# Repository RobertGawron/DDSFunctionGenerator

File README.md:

# 6MHz DDS Function Generator

**This project is unfinished.**

## Summary

A function generator is a laboratory instrument used to generate various electrical waveforms. This project utilizes DDS  [DDS (direct digital synthesis)](https://en.wikipedia.org/wiki/Direct_digital_synthesis), a technique that allows the creation of arbitrary waveforms from a single base frequency.

## Current Version

The current version of the PCB uses components with 0402 (or similar) footprints. Use of these components wasn’t the best choice - they're too difficult to solder, and there was no need to minimize the board size. The next version of the PCB will switch to 0805 components for easier assembly.

## System Architecture

Tools: PlantUML

## Hardware

Tools: KiCad (for PCB design).

## Software

Tools:
* **Business Logic:** Written in Forth, a stack-based programming language designed for embedded systems and control applications.
* **Drivers:** Developed in C++17.
* **Hardware Abstraction Layer (HAL):** Auto-generated using CubeMX, a tool from STMicroelectronics.

## Simulation

This project includes an LCD for user interaction. To simplify the creation of the layout, a simulation environment has been developed. 

This simulation combines the following:
* **UI:** Built using PyQt for rendering the LCD layout and facilitating user interaction.
* **Business Logic:** Reuses the core firmware logic directly from the hardware codebase.
* HAL and Driver Mocks: Created in C++.

[More Info](./Simulation/FirmwarePCSimulator/README.md)

## Enclosure

The device's enclosure is designed using **OpenSCAD**, a script-based 3D CAD modeler that allows precise and parametric design.

[More Info](./Mechanic/MechanicOverview/README.md)

## Devops

Repetitive setup tasks are best left to automation, which is why the development environment is managed with Docker. This approach eliminates the need to deal with outdated installation lists or READMEs—just run the container, and everything is ready to go.

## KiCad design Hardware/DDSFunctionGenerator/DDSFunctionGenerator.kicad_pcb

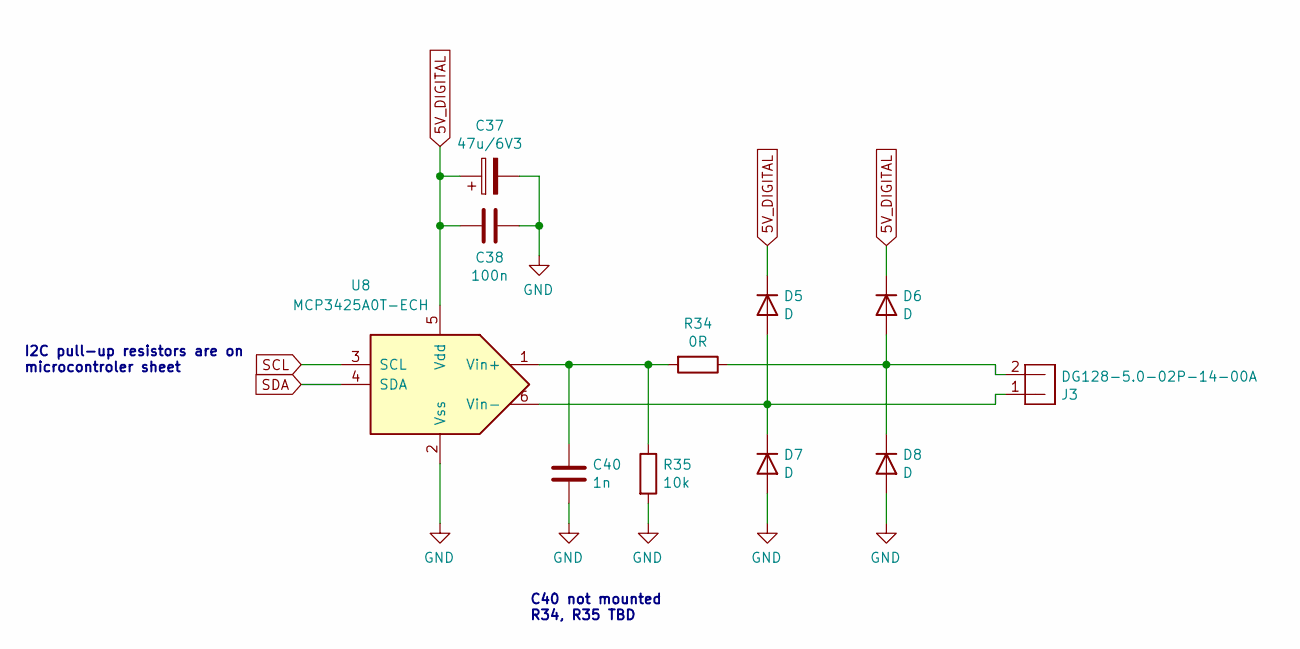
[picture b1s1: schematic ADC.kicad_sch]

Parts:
C37: 47u/6V3; CP_EIA-3528-21_Kemet-B
C38: 100n; C_0805_2012Metric
C40: 1n; C_0805_2012Metric
D5, D6, D7, D8: D; D_MiniMELF
J3: DG128-5.0-02P-14-00A
R34: 0R; R_0805_2012Metric
R35: 10k; R_0805_2012Metric
U8: MCP3425A0T-ECH; SOT-23-6_Handsoldering

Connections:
5V_DIGITAL: C37.1, C38.2, D5.1 (K), D6.1 (K), U8.5 (Vdd); also elsewhere on the board
GND: C37.2, C38.1, C40.2, D7.2 (A), D8.2 (A), R35.2, U8.2 (Vss); also elsewhere on the board
unnamed: D5.2 (A), D7.1 (K), J3.1, U8.6 (Vin-)
unnamed: D6.2 (A), D8.1 (K), J3.2, R34.1
unnamed: C40.1, R34.2, R35.1, U8.1 (Vin+)
SCL: U8.3 (SCL); also elsewhere on the board
SDA: U8.4 (SDA); also elsewhere on the board

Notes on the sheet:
I2C pull-up resistors are on microcontroler sheet
C40 not mounted R34, R35 TBD

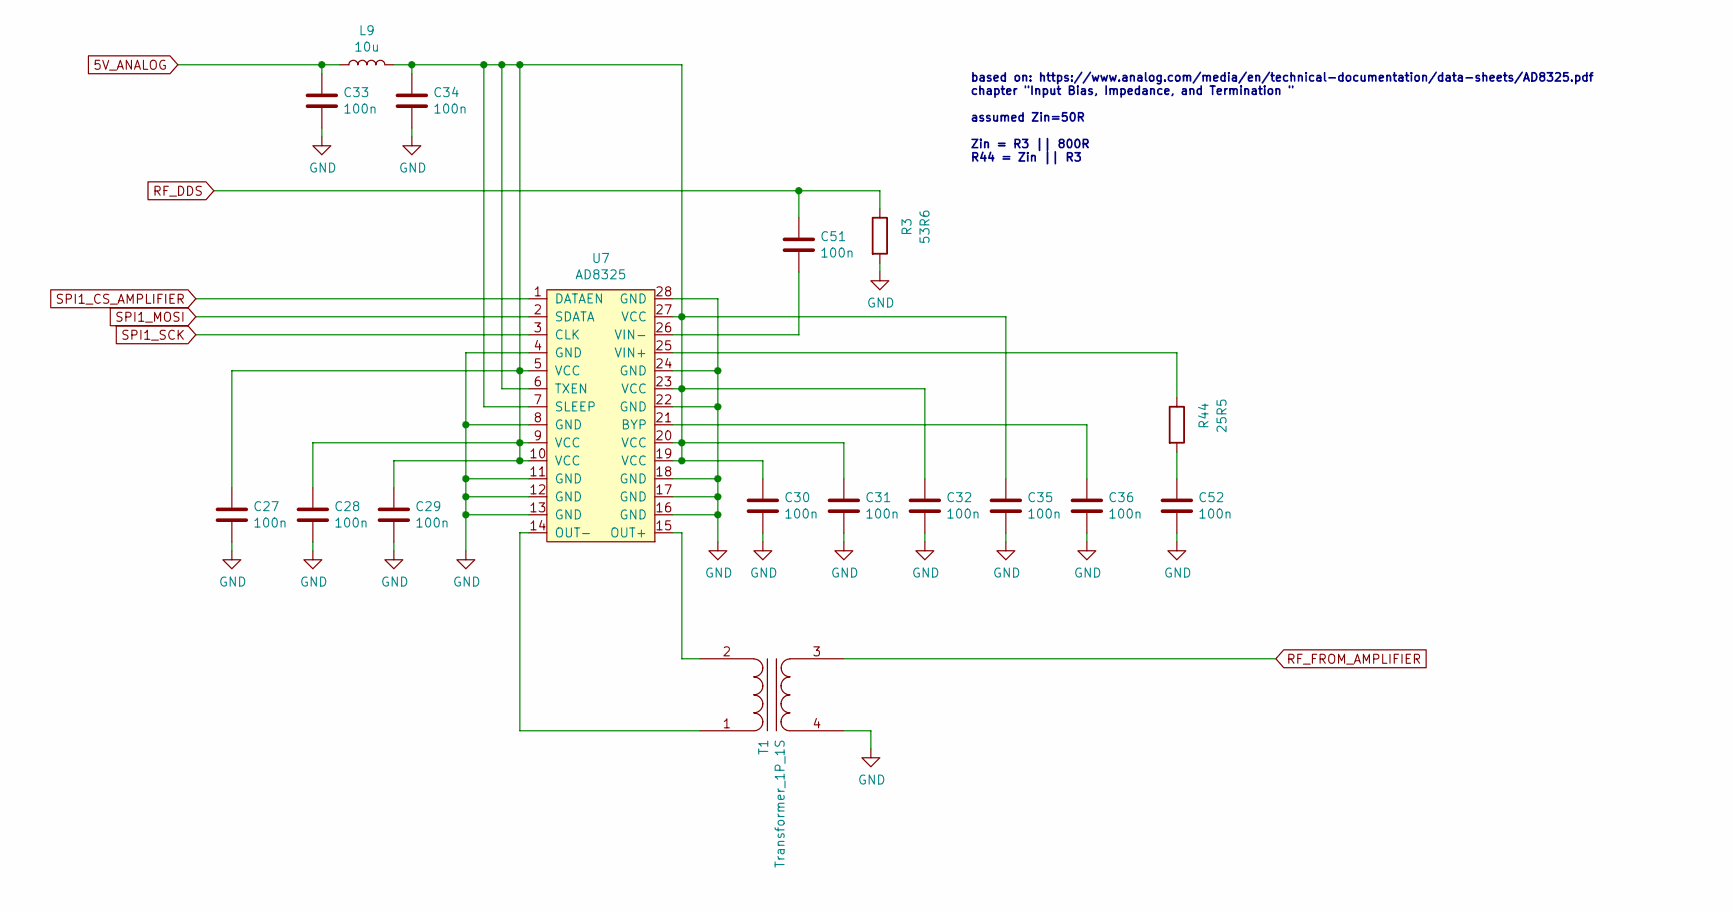
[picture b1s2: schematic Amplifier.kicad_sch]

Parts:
C27, C28, C29, C30, C31, C32, C33, C34, C35, C36, C51, C52: 100n; C_0805_2012Metric
L9: 10u; L_0805_2012Metric
R3: 53R6; R_0805_2012Metric
R44: 25R5; R_0805_2012Metric
T1: Transformer_1P_1S; Transformer_B62152_8.3
U7: AD8325; TSSOP-28_4.4x9.7mm_P0.65mm

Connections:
5V_ANALOG: C33.1, L9.1; also elsewhere on the board
GND: C27.2, C28.2, C29.1, C30.2, C31.2, C32.2, C33.2, C34.2, C35.2, C36.2, C52.2, R3.2, T1.4 (SB), U7.4 (GND), U7.8 (GND), U7.11 (GND), U7.12 (GND), U7.13 (GND), U7.16 (GND), U7.17 (GND), U7.18 (GND), U7.22 (GND), U7.24 (GND), U7.28 (GND); also elsewhere on the board
unnamed: C52.1, R44.2
unnamed: T1.1 (AA), U7.14 (OUT-)
unnamed: T1.2 (AB), U7.15 (OUT+)
unnamed: C36.1, U7.21 (BYP)
unnamed: C27.1, C28.1, C29.2, C30.1, C31.1, C32.1, C34.1, C35.1, L9.2, U7.5 (VCC), U7.6 (TXEN), U7.7 (SLEEP), U7.9 (VCC), U7.10 (VCC), U7.19 (VCC), U7.20 (VCC), U7.23 (VCC), U7.27 (VCC)
unnamed: R44.1, U7.25 (VIN+)
unnamed: C51.2, U7.26 (VIN-)
RF_DDS: C51.1, R3.1; also elsewhere on the board
RF_FROM_AMPLIFIER: T1.3 (SA); also elsewhere on the board
SPI1_CS_AMPLIFIER: U7.1 (DATAEN); also elsewhere on the board
SPI1_MOSI: U7.2 (SDATA); also elsewhere on the board
SPI1_SCK: U7.3 (CLK); also elsewhere on the board

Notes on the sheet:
based on: https://www.analog.com/media/en/technical-documentation/data-sheets/AD8325.pdf chapter "Input Bias, Impedance, and Termination " assumed Zin=50R Zin = R3 || 800R R44 = Zin || R3

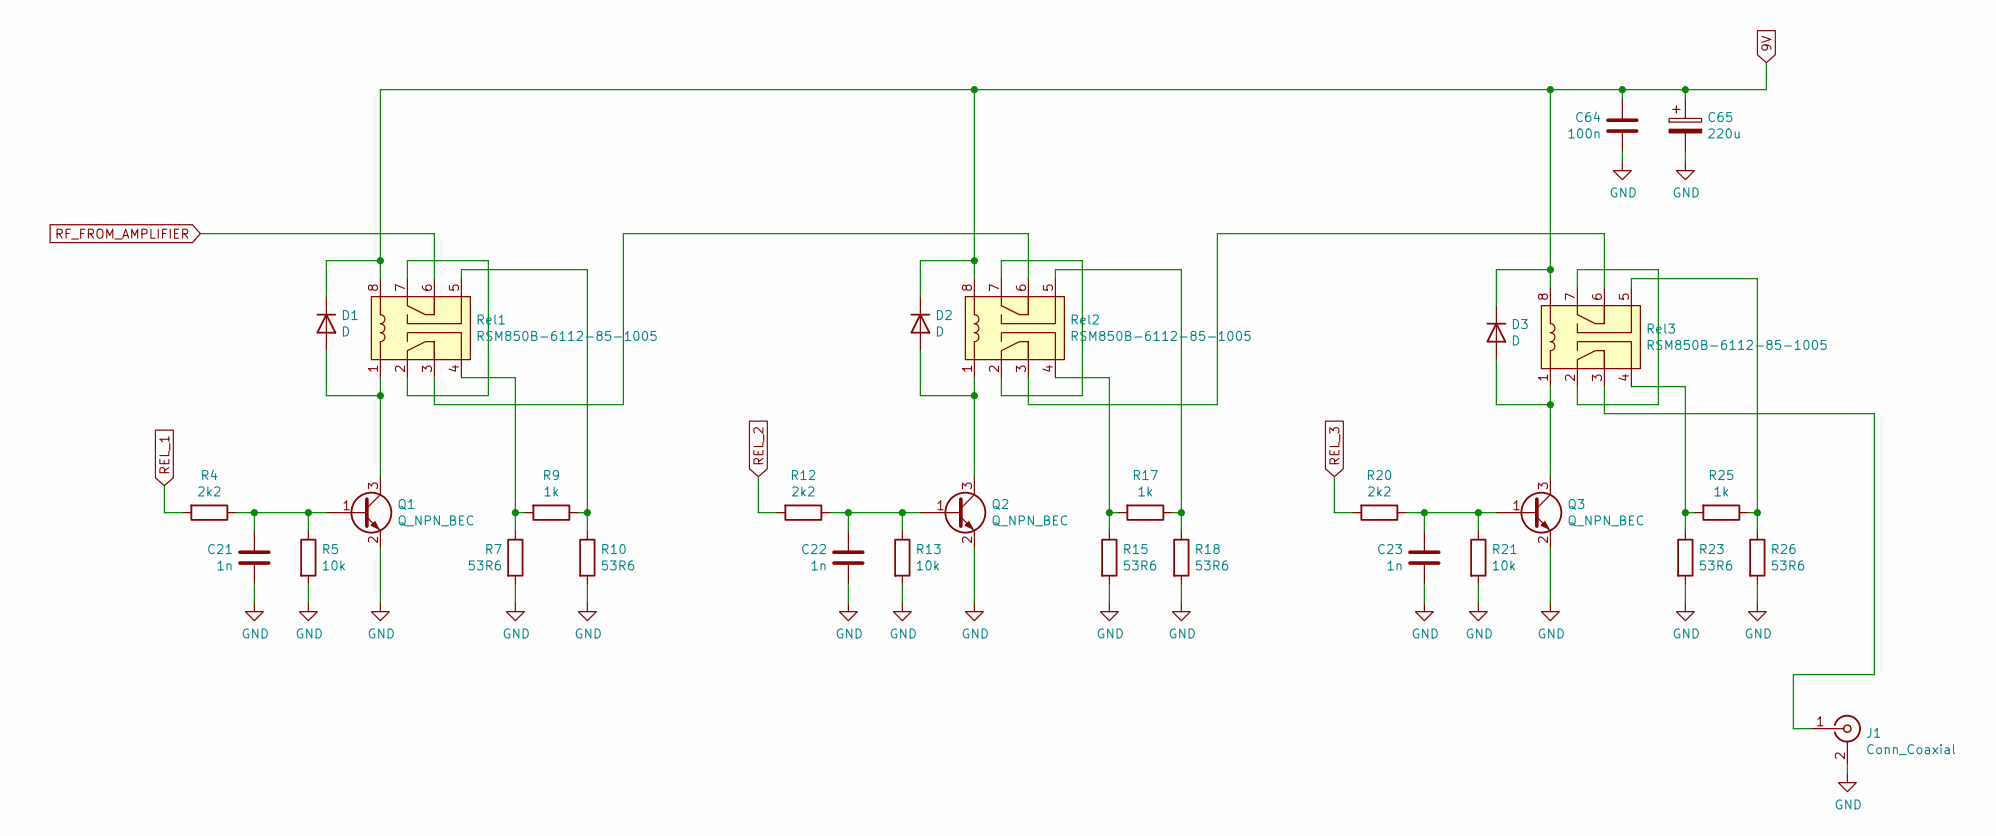
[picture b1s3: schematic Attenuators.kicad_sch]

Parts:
C21, C22, C23: 1n; C_0805_2012Metric
C64: 100n; C_0805_2012Metric
C65: 220u; CP_Elec_6.3x5.8
D1, D2, D3: D; D_MiniMELF
J1: Conn_Coaxial; BNC_Amphenol_B6252HB-NPP3G-50_Horizontal
Q1, Q2, Q3: Q_NPN_BEC; SOT-323_SC-70
R4, R12, R20: 2k2; R_0805_2012Metric
R5, R13, R21: 10k; R_0805_2012Metric
R7, R10, R15, R18, R23, R26: 53R6; R_0805_2012Metric
R9, R17, R25: 1k; R_0805_2012Metric
Rel1, Rel2, Rel3: RSM850B-6112-85-1005; Relay_DPDT_Omron_G6K-2P-Y

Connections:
9V: C64.1, C65.1, D1.1 (K), D2.1 (K), D3.1 (K), Rel1.8, Rel2.8, Rel3.8; also elsewhere on the board
GND: C21.2, C22.2, C23.2, C64.2, C65.2, J1.2 (Ext), Q1.2 (E), Q2.2 (E), Q3.2 (E), R5.2, R7.2, R10.2, R13.2, R15.2, R18.2, R21.2, R23.2, R26.2; also elsewhere on the board
unnamed: D1.2 (A), Q1.3 (C), Rel1.1
unnamed: D2.2 (A), Q2.3 (C), Rel2.1
unnamed: D3.2 (A), Q3.3 (C), Rel3.1
unnamed: J1.1 (In), Rel3.3
unnamed: C21.1, Q1.1 (B), R4.1, R5.1
unnamed: C22.1, Q2.1 (B), R12.1, R13.1
unnamed: C23.1, Q3.1 (B), R20.1, R21.1
unnamed: R7.1, R9.2, Rel1.4
unnamed: R9.1, R10.1, Rel1.5
unnamed: R15.1, R17.2, Rel2.4
unnamed: R17.1, R18.1, Rel2.5
unnamed: R23.1, R25.2, Rel3.4
unnamed: R25.1, R26.1, Rel3.5
unnamed: Rel1.2, Rel1.7
unnamed: Rel1.3, Rel2.6
unnamed: Rel2.2, Rel2.7
unnamed: Rel2.3, Rel3.6
unnamed: Rel3.2, Rel3.7
REL_1: R4.2; also elsewhere on the board
REL_2: R12.2; also elsewhere on the board
REL_3: R20.2; also elsewhere on the board
RF_FROM_AMPLIFIER: Rel1.6; also elsewhere on the board

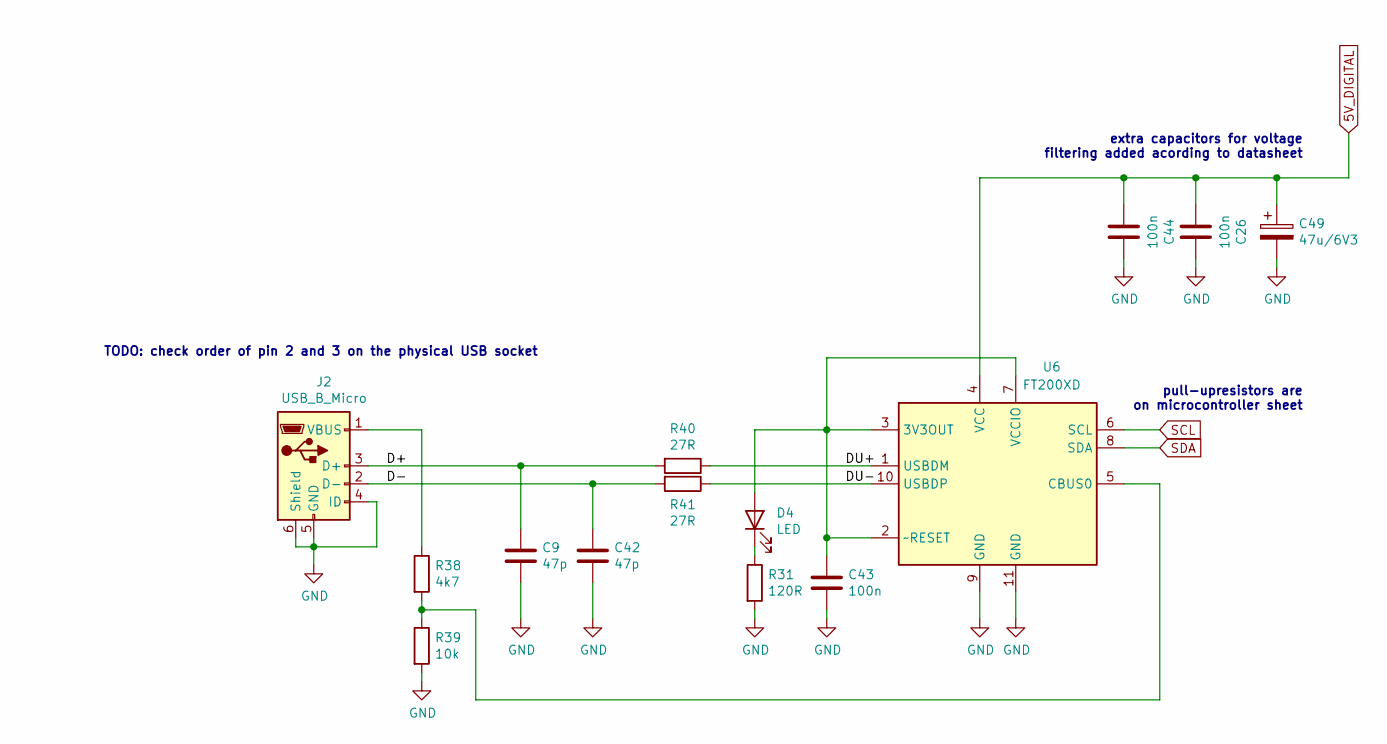
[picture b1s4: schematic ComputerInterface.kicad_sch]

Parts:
C9, C42: 47p; C_0805_2012Metric
C26, C43, C44: 100n; C_0805_2012Metric
C49: 47u/6V3; CP_EIA-3528-21_Kemet-B
D4: LED; LED_0402_1005Metric
J2: USB_B_Micro; USB_Micro-B_Molex_47346-0001
R31: 120R; R_0805_2012Metric
R38: 4k7; R_0805_2012Metric
R39: 10k; R_0805_2012Metric
R40, R41: 27R; R_0805_2012Metric
U6: FT200XD; DFN-10-1EP_3x3mm_P0.5mm_EP1.55x2.48mm

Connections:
5V_DIGITAL: C26.1, C44.1, C49.1, U6.4 (VCC); also elsewhere on the board
/ComputerInterface/D+: C9.2, J2.3 (D+), R40.2
/ComputerInterface/D-: C42.2, J2.2 (D-), R41.2
/ComputerInterface/DU+: R40.1, U6.1 (USBDM)
/ComputerInterface/DU-: R41.1, U6.10 (USBDP)
GND: C9.1, C26.2, C42.1, C43.1, C44.2, C49.2, J2.4 (ID), J2.5 (GND), J2.6 (Shield), R31.2, R39.2, U6.9 (GND), U6.11 (GND); also elsewhere on the board
unnamed: C43.2, D4.2 (A), U6.2 (~RESET), U6.3 (3V3OUT), U6.7 (VCCIO)
unnamed: D4.1 (K), R31.1
unnamed: J2.1 (VBUS), R38.1
unnamed: R38.2, R39.1, U6.5 (CBUS0)
SCL: U6.6 (SCL); also elsewhere on the board
SDA: U6.8 (SDA); also elsewhere on the board

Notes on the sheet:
extra capacitors for voltage filtering added acording to datasheet
TODO: check order of pin 2 and 3 on the physical USB socket
pull-upresistors are on microcontroller sheet

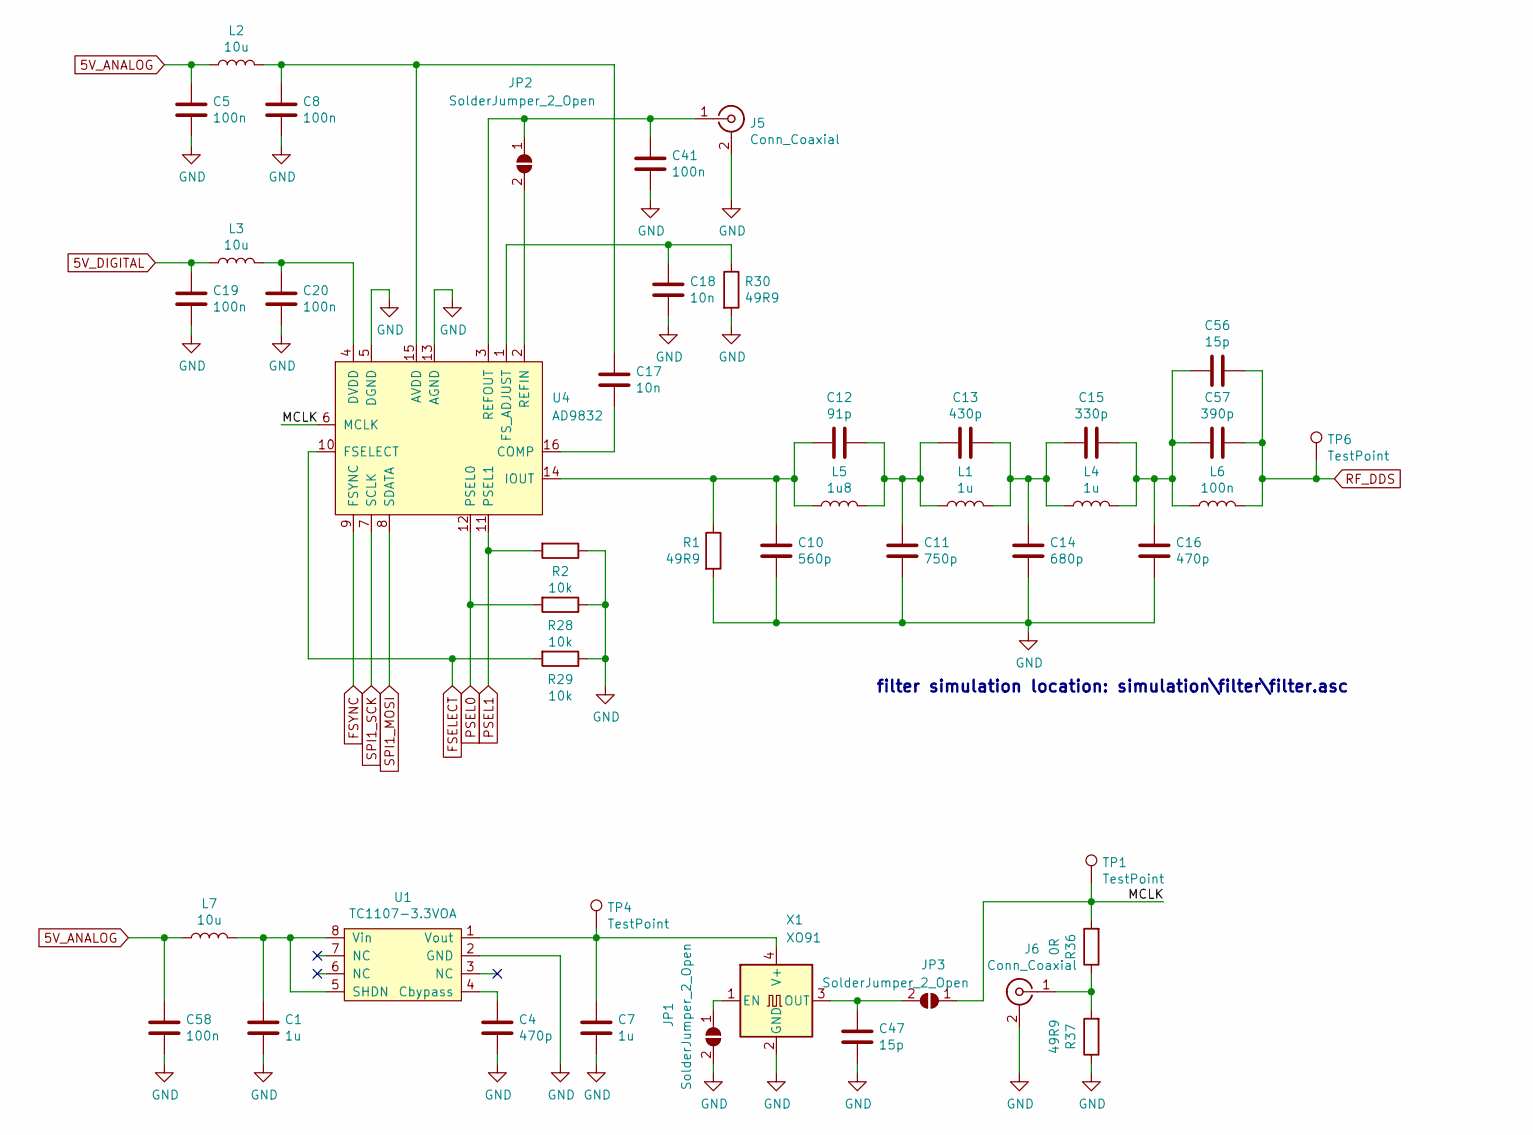
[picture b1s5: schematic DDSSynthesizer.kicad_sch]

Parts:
C1, C7: 1u; C_0805_2012Metric
C4, C16: 470p; C_0805_2012Metric
C5, C8, C19, C20, C41, C58: 100n; C_0805_2012Metric
C10: 560p; C_0805_2012Metric
C11: 750p; C_0805_2012Metric
C12: 91p; C_0805_2012Metric
C13: 430p; C_0805_2012Metric
C14: 680p; C_0805_2012Metric
C15: 330p; C_0805_2012Metric
C17, C18: 10n; C_0805_2012Metric
C47, C56: 15p; C_0805_2012Metric
C57: 390p; C_0805_2012Metric
J5, J6: Conn_Coaxial; U.FL_Molex_MCRF_73412-0110_Vertical
JP1, JP2, JP3: SolderJumper_2_Open; SolderJumper-2_P1.3mm_Open_RoundedPad1.0x1.5mm
L1, L4: 1u; L_0805_2012Metric
L2, L3, L7: 10u; L_0805_2012Metric
L5: 1u8; L_0805_2012Metric
L6: 100n; L_0805_2012Metric
R1, R30, R37: 49R9; R_0805_2012Metric
R2, R28, R29: 10k; R_0805_2012Metric
R36: 0R; R_0805_2012Metric
TP1, TP4, TP6: TestPoint; TestPoint_Pad_1.0x1.0mm
U1: TC1107-3.3VOA; SOIC-8_3.9x4.9mm_P1.27mm
U4: AD9832; TSSOP-16_4.4x5mm_P0.65mm
X1: XO91; LF_SPXO018035

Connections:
5V_ANALOG: C5.1, C58.1, L2.1, L7.1; also elsewhere on the board
5V_DIGITAL: C19.1, L3.1; also elsewhere on the board
/DDSSynthesizer/MCLK: JP3.1 (A), R36.2, TP1.1, U4.6 (MCLK)
FSELECT: R29.2, U4.10 (FSELECT); also elsewhere on the board
FSYNC: U4.9 (FSYNC); also elsewhere on the board
GND: C1.1, C4.1, C5.2, C7.1, C8.2, C10.1, C11.1, C14.1, C16.1, C18.2, C19.2, C20.2, C41.2, C47.1, C58.2, J5.2 (Ext), J6.2 (Ext), JP1.2 (B), R1.2, R2.1, R28.1, R29.1, R30.2, R37.1, U1.2 (GND), U4.5 (DGND), U4.13 (AGND), X1.2 (GND); also elsewhere on the board
unnamed: C11.2, C12.2, C13.1, L1.1, L5.2
unnamed: C13.2, C14.2, C15.1, L1.2, L4.1
unnamed: C15.2, C16.2, C56.1, C57.1, L4.2, L6.1
unnamed: C41.1, J5.1 (In), JP2.1 (A), U4.3 (REFOUT)
unnamed: J6.1 (In), R36.1, R37.2
unnamed: JP1.1 (A), X1.1 (EN)
unnamed: JP2.2 (B), U4.2 (REFIN)
unnamed: C47.2, JP3.2 (B), X1.3 (OUT)
unnamed: C4.2, U1.4 (Cbypass)
unnamed: C1.2, L7.2, U1.5 (SHDN), U1.8 (Vin)
unnamed: C7.2, TP4.1, U1.1 (Vout), X1.4 (V+)
unnamed: C8.1, C17.1, L2.2, U4.15 (AVDD)
unnamed: C17.2, U4.16 (COMP)
unnamed: C20.1, L3.2, U4.4 (DVDD)
unnamed: C18.1, R30.1, U4.1 (FS_ADJUST)
unnamed: C10.2, C12.1, L5.1, R1.1, U4.14 (IOUT)
PSEL0: R28.2, U4.12 (PSEL0); also elsewhere on the board
PSEL1: R2.2, U4.11 (PSEL1); also elsewhere on the board
RF_DDS: C56.2, C57.2, L6.2, TP6.1; also elsewhere on the board
SPI1_MOSI: U4.8 (SDATA); also elsewhere on the board
SPI1_SCK: U4.7 (SCLK); also elsewhere on the board

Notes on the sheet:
filter simulation location: simulation\filter\filter.asc

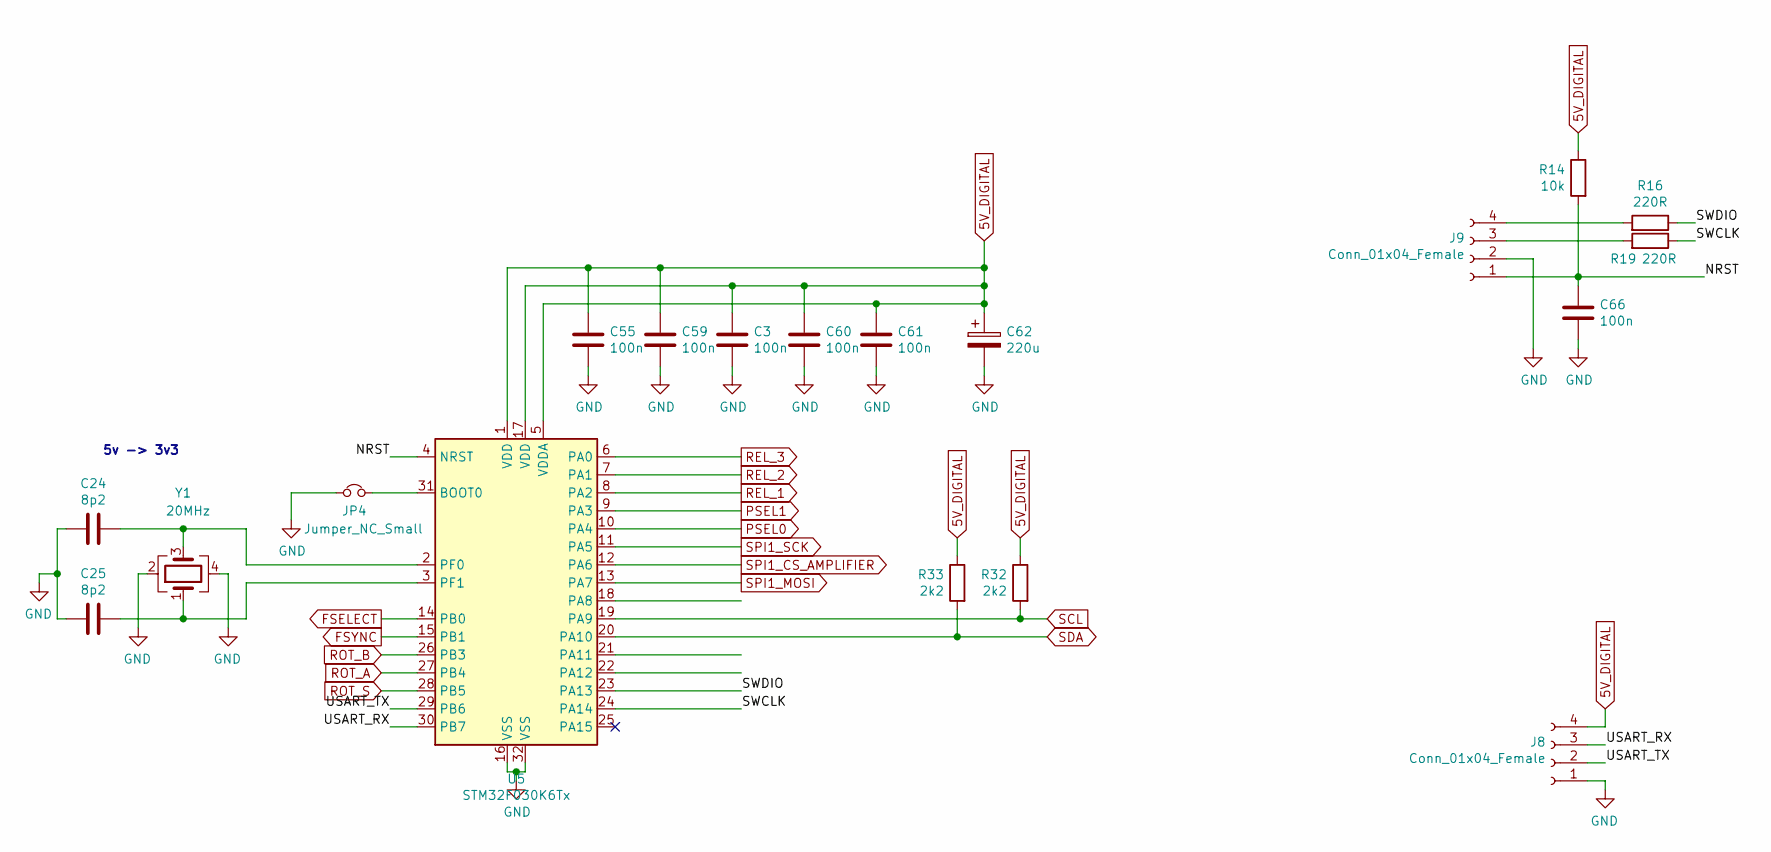
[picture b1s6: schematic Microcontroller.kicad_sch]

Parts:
C3, C55, C59, C60, C61, C66: 100n; C_0805_2012Metric
C24, C25: 8p2; C_0805_2012Metric
C62: 220u; CP_Elec_6.3x5.8
J8, J9: Conn_01x04_Female; PinHeader_1x04_P2.54mm_Vertical
JP4: Jumper_NC_Small; SolderJumper-2_P1.3mm_Bridged2Bar_RoundedPad1.0x1.5mm
R14: 10k; R_0805_2012Metric
R16, R19: 220R; R_0805_2012Metric
R32, R33: 2k2; R_0805_2012Metric
U5: STM32F030K6Tx; LQFP-32_7x7mm_P0.8mm
Y1: 20MHz; Oscillator_SMD_EuroQuartz_XO53-4Pin_5.0x3.2mm

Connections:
5V_DIGITAL: C3.1, C55.1, C59.1, C60.1, C61.1, C62.1, J8.4, R14.1, R32.1, R33.1, U5.1 (VDD), U5.5 (VDDA), U5.17 (VDD); also elsewhere on the board
/Microcontroller/NRST: C66.1, J9.1, R14.2, U5.4 (NRST)
/Microcontroller/SWCLK: R19.1, U5.24 (PA14)
/Microcontroller/SWDIO: R16.1, U5.23 (PA13)
/Microcontroller/USART_RX: J8.3, U5.30 (PB7)
/Microcontroller/USART_TX: J8.2, U5.29 (PB6)
FSELECT: U5.14 (PB0); also elsewhere on the board
FSYNC: U5.15 (PB1); also elsewhere on the board
GND: C3.2, C24.1, C25.1, C55.2, C59.2, C60.2, C61.2, C62.2, C66.2, J8.1, J9.2, JP4.1, U5.16 (VSS), U5.32 (VSS), Y1.2, Y1.4; also elsewhere on the board
unnamed: J9.3, R19.2
unnamed: J9.4, R16.2
unnamed: JP4.2, U5.31 (BOOT0)
unnamed: C24.2, U5.2 (PF0), Y1.3
unnamed: C25.2, U5.3 (PF1), Y1.1
PSEL0: U5.10 (PA4); also elsewhere on the board
PSEL1: U5.9 (PA3); also elsewhere on the board
REL_1: U5.8 (PA2); also elsewhere on the board
REL_2: U5.7 (PA1); also elsewhere on the board
REL_3: U5.6 (PA0); also elsewhere on the board
ROT_A: U5.26 (PB3), U5.27 (PB4); also elsewhere on the board
ROT_S: U5.28 (PB5); also elsewhere on the board
SCL: R32.2, U5.19 (PA9); also elsewhere on the board
SDA: R33.2, U5.20 (PA10); also elsewhere on the board
SPI1_CS_AMPLIFIER: U5.12 (PA6); also elsewhere on the board
SPI1_MOSI: U5.13 (PA7); also elsewhere on the board
SPI1_SCK: U5.11 (PA5); also elsewhere on the board

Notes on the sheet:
5v -> 3v3

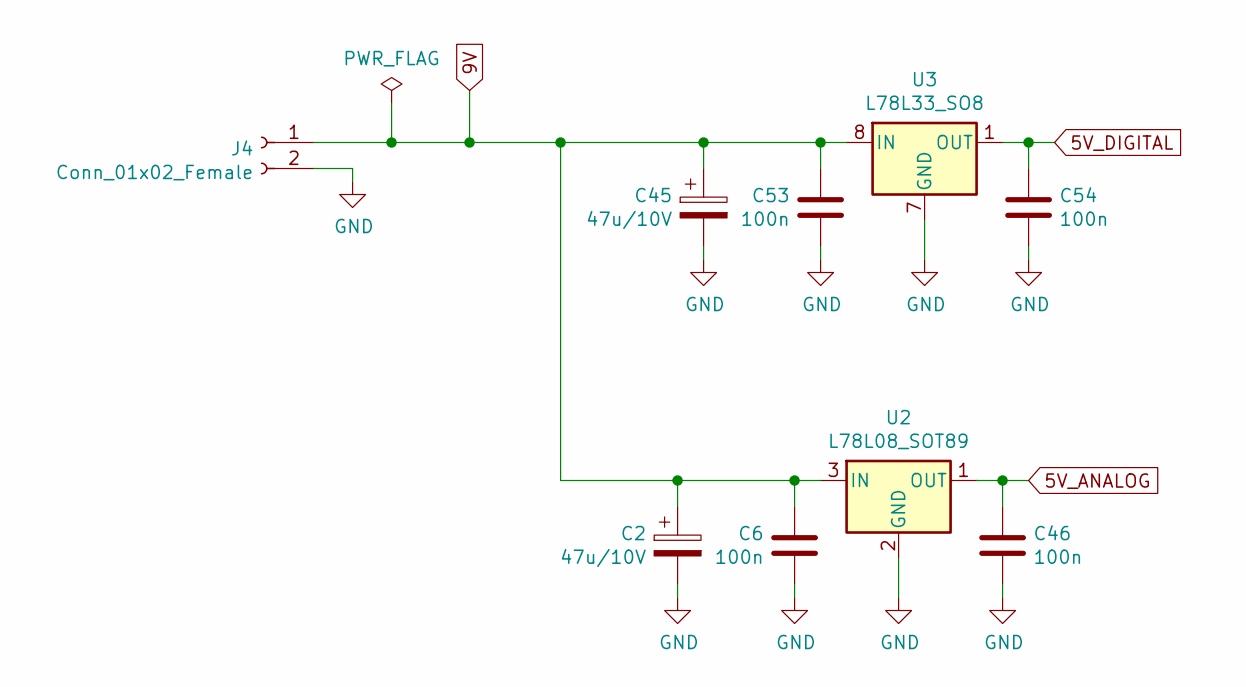
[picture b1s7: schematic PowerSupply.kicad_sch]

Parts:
C2, C45: 47u/10V; CP_EIA-3528-21_Kemet-B
C6, C46, C53, C54: 100n; C_0805_2012Metric
J4: Conn_01x02_Female; DG128-5.0-02P-14-00A
U2: L78L08_SOT89; SOT-89-3
U3: L78L33_SO8; SOIC-8_3.9x4.9mm_P1.27mm

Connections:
5V_ANALOG: C46.1, U2.1 (OUT); also elsewhere on the board
5V_DIGITAL: C54.1, U3.1 (OUT); also elsewhere on the board
9V: C2.1, C6.1, C45.1, C53.1, J4.1, U2.3 (IN), U3.8 (IN); also elsewhere on the board
GND: C2.2, C6.2, C45.2, C46.2, C53.2, C54.2, J4.2, U2.2 (GND), U3.2 (GND), U3.3 (GND), U3.6 (GND), U3.7 (GND); also elsewhere on the board

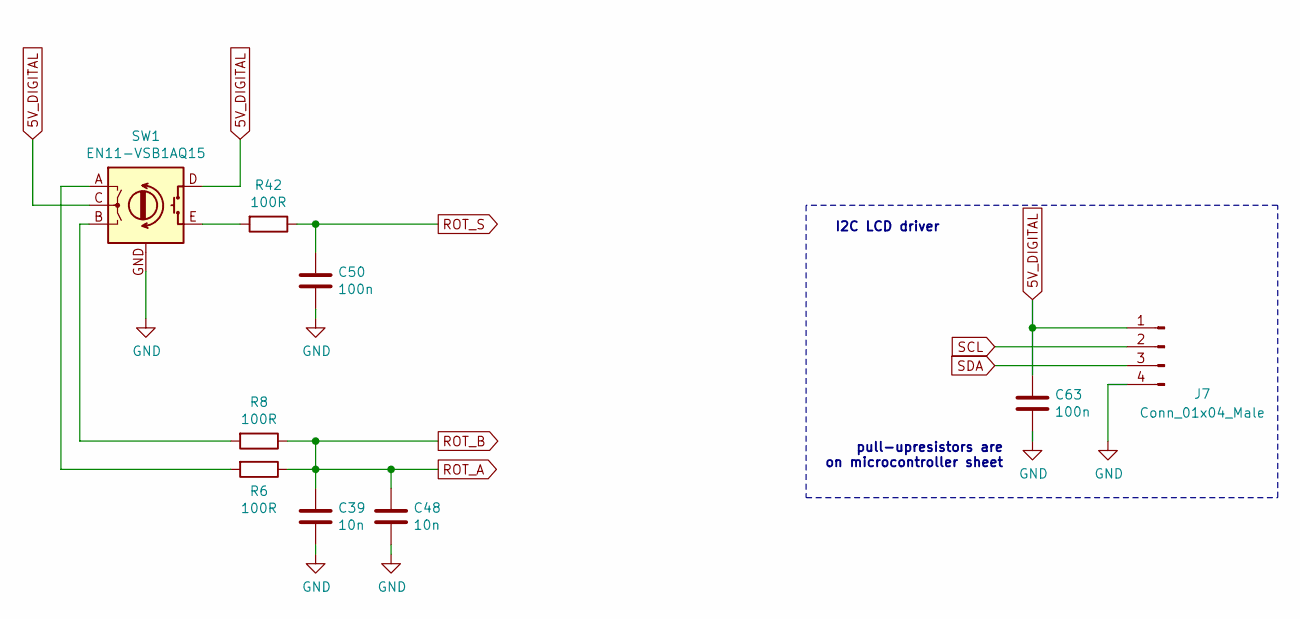
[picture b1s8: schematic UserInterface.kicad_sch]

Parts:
C39, C48: 10n; C_0402_1005Metric
C50: 100n; C_0402_1005Metric
C63: 100n; C_0805_2012Metric
J7: Conn_01x04_Male; PinHeader_1x04_P2.54mm_Vertical
R6, R8, R42: 100R; R_0402_1005Metric
SW1: EN11-VSB1AQ15; EN11-VNB1BQ15

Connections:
5V_DIGITAL: C63.1, J7.1, SW1.C, SW1.D; also elsewhere on the board
GND: C39.2, C48.2, C50.2, C63.2, J7.4, SW1.GND; also elsewhere on the board
unnamed: R6.2, SW1.A
unnamed: R8.2, SW1.B
unnamed: R42.2, SW1.E
ROT_A: C39.1, C48.1, R6.1, R8.1; also elsewhere on the board
ROT_S: C50.1, R42.1; also elsewhere on the board
SCL: J7.2; also elsewhere on the board
SDA: J7.3; also elsewhere on the board

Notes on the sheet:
pull-upresistors are on microcontroller sheet
I2C LCD driver

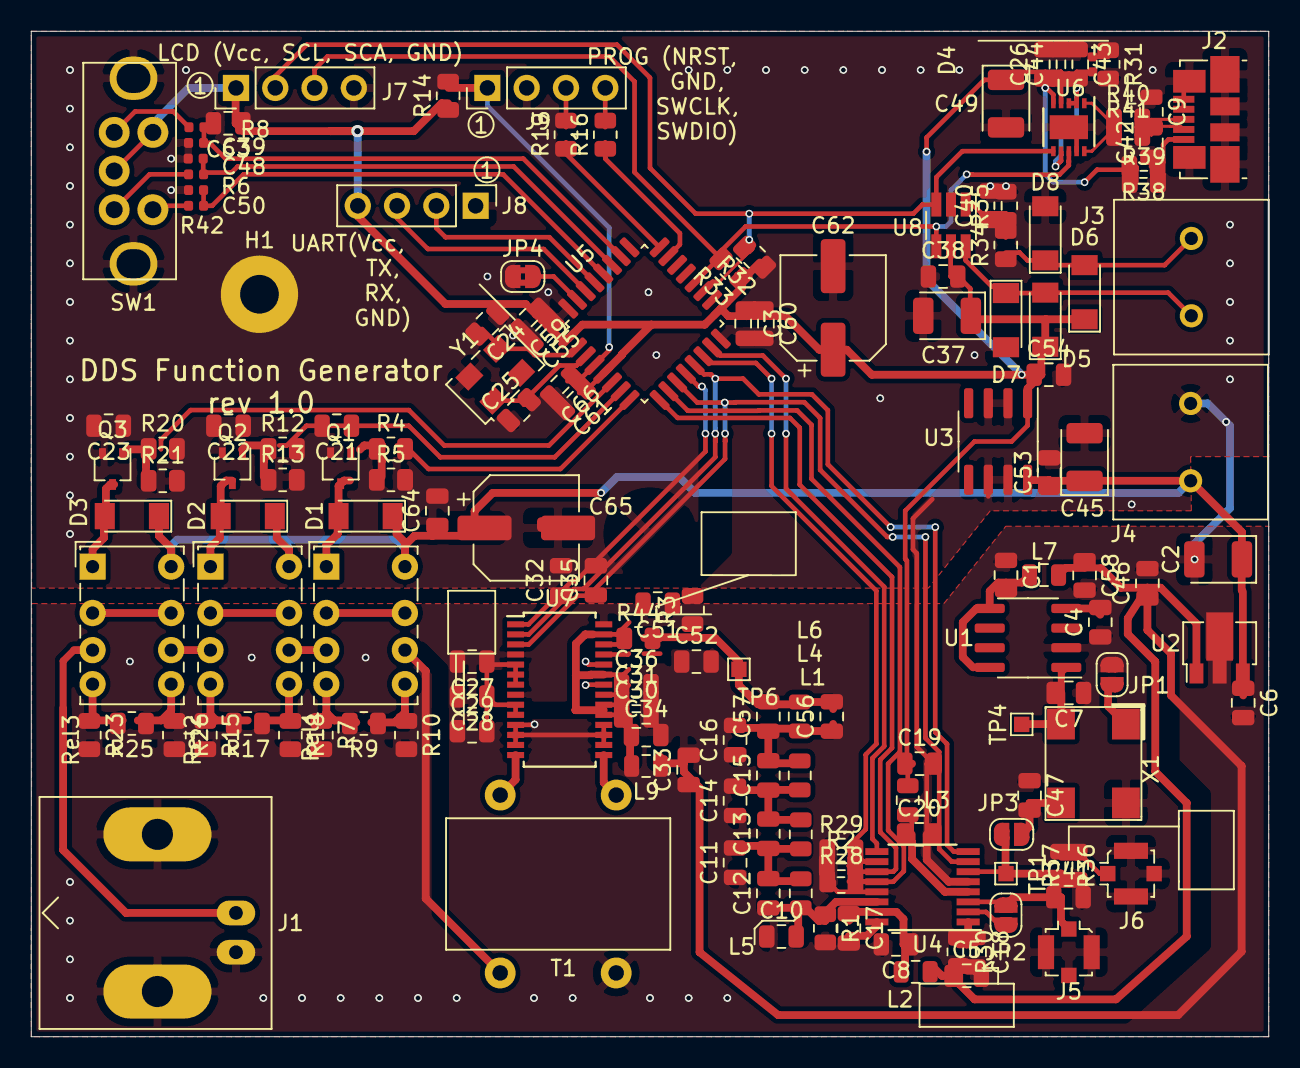
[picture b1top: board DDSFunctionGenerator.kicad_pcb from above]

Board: 2 copper layers, 80.0 x 65.0 mm, 156 parts (0 on the bottom side), 86 nets.

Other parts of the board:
H1: MountingHole_Pad; MountingHole_2.5mm_Pad

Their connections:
GND: H1.1; also elsewhere on the board

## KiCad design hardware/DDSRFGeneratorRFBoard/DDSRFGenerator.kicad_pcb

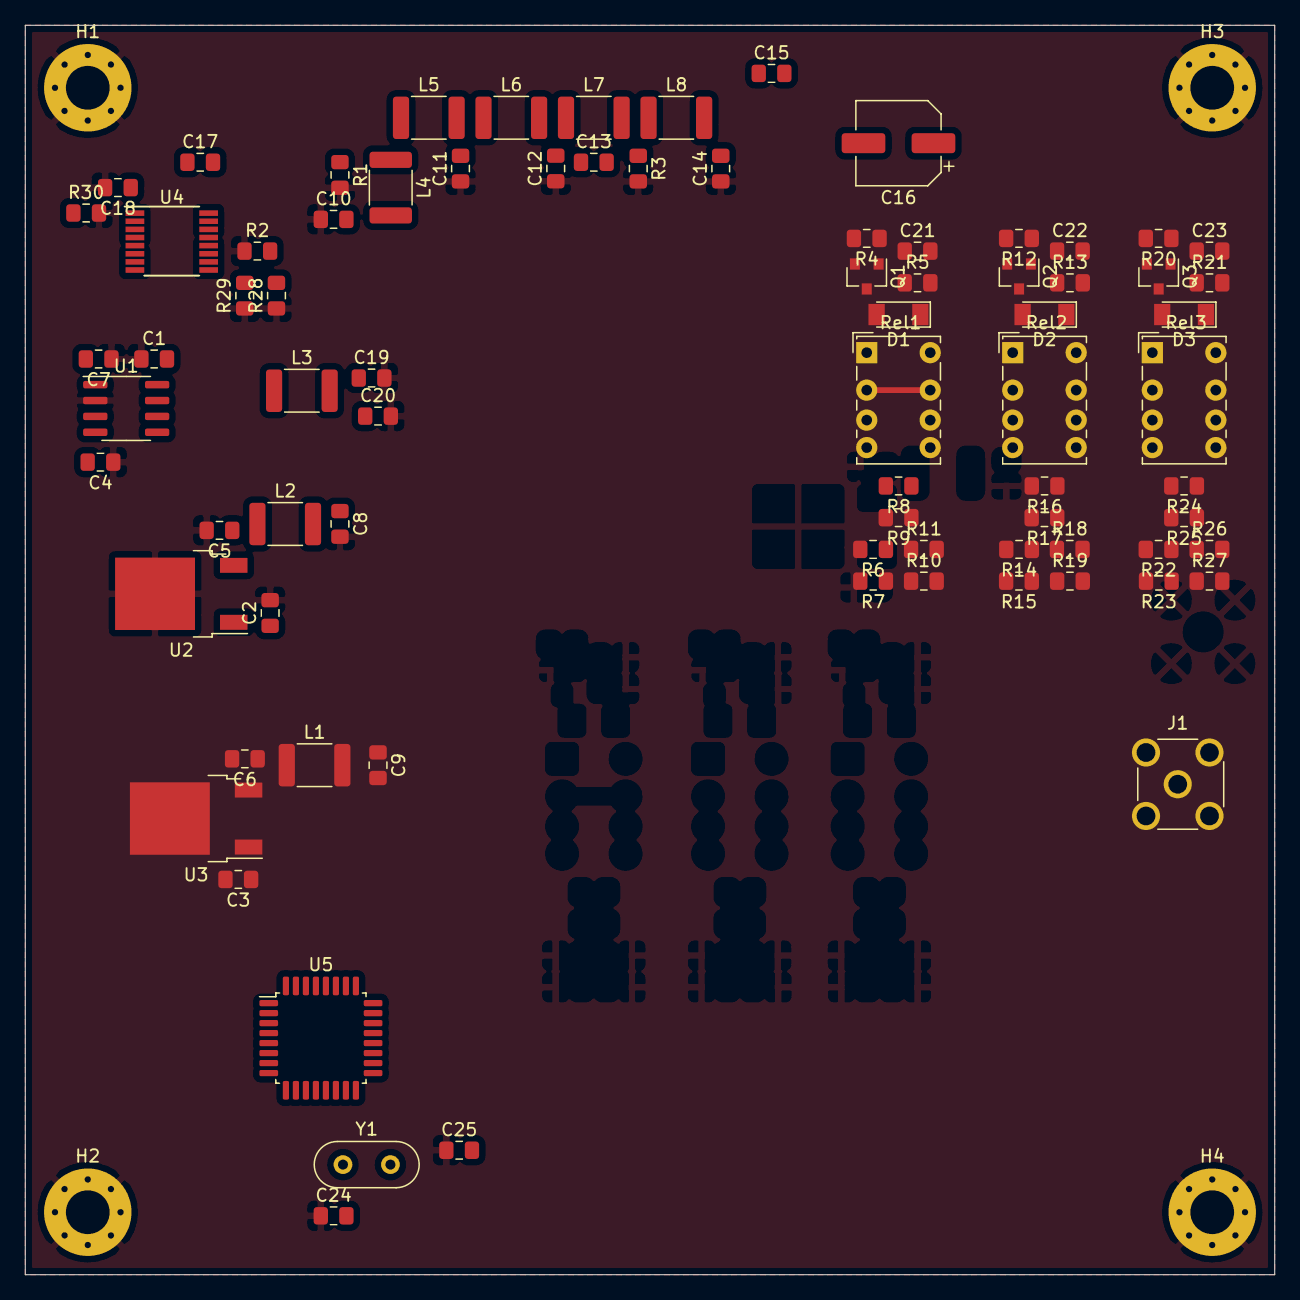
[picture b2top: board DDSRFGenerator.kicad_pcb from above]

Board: 2 copper layers, 100.0 x 100.0 mm, 83 parts (0 on the bottom side), 43 nets.

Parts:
C1, C7: 1u; C_0805_2012Metric_Pad1.15x1.40mm_HandSolder
C2, C3, C5, C6, C8, C9, C15, C19, C20: 100n; C_0805_2012Metric_Pad1.15x1.40mm_HandSolder
C4: 470p; C_0805_2012Metric_Pad1.15x1.40mm_HandSolder
C10, C14: 18p; C_0805_2012Metric_Pad1.15x1.40mm_HandSolder
C11, C12: 68p; C_0805_2012Metric_Pad1.15x1.40mm_HandSolder
C13: 5p6; C_0805_2012Metric_Pad1.15x1.40mm_HandSolder
C16: 22u/10V; CP_Elec_6.3x5.4
C17, C18: 10n; C_0805_2012Metric_Pad1.15x1.40mm_HandSolder
C21, C22, C23: 1n; C_0805_2012Metric_Pad1.15x1.40mm_HandSolder
C24, C25: 20p; C_0805_2012Metric_Pad1.15x1.40mm_HandSolder
D1, D2, D3: D; D_MiniMELF
H1, H2, H3, H4: MountingHole_Pad; MountingHole_3.5mm_Pad_Via
J1: Conn_Coaxial; SMA_Molex_73251-2200_Horizontal
L1, L2, L3: 4u7; L_1812_4532Metric_Pad1.30x3.40mm_HandSolder
L4: 120n; L_1812_4532Metric_Pad1.30x3.40mm_HandSolder
L5, L7, L8: 150n; L_1812_4532Metric_Pad1.30x3.40mm_HandSolder
L6: 220n; L_1812_4532Metric_Pad1.30x3.40mm_HandSolder
Q1, Q2, Q3: Q_NPN_BEC; SOT-23
R1, R3, R30: 49R9; R_0805_2012Metric_Pad1.15x1.40mm_HandSolder
R2, R5, R13, R21, R28, R29: 10k; R_0805_2012Metric_Pad1.15x1.40mm_HandSolder
R4, R12, R20: 2k2; R_0805_2012Metric_Pad1.15x1.40mm_HandSolder
R6, R7, R10, R11, R14, R15, R18, R19, R22, R23, R26, R27: 105R; R_0805_2012Metric_Pad1.15x1.40mm_HandSolder
R8, R16, R24: 1k69; R_0805_2012Metric_Pad1.15x1.40mm_HandSolder
R9, R17, R25: 2k; R_0805_2012Metric_Pad1.15x1.40mm_HandSolder
Rel1, Rel2, Rel3: RSM850B-6112-85-1005; Relay_DPDT_Omron_G6K-2P-Y
U1: TC1107-3.3VOA; SOIC-8_3.9x4.9mm_P1.27mm
U2, U3: L7805; TO-252-2
U4: AD9832; TSSOP-16_4.4x5mm_P0.65mm
U5: STM32F030K6Tx; LQFP-32_7x7mm_P0.8mm
Y1: Crystal; Crystal_HC52-6mm_Vertical

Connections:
5V_DIGITAL: C19.1, L3.1
+9V: D1.1, D2.1, D3.1, Rel1.8, Rel2.8, Rel3.8
FSELECT: R29.2, U4.10
GND: C1.1, C2.2, C3.2, C4.1, C5.2, C6.2, C7.1, C8.2, C9.2, C10.1, C11.1, C12.1, C14.1, C18.2, C19.2, C20.2, C21.2, C22.2, C23.2, C24.1, C25.1, H1.1, H2.1, H3.1, H4.1, J1.2, Q1.2, Q2.2, Q3.2, R1.2, R2.1, R3.2, R5.2, R6.2, R7.2, R10.2, R11.2, R13.2, R14.2, R15.2, R18.2, R19.2, R21.2, R22.2, R23.2, R26.2, R27.2, R28.1, R29.1, R30.2, U1.2, U2.2, U3.2, U4.5, U4.13
unnamed: C4.2, U1.4
unnamed: C5.1, L2.1, U2.3
unnamed: C6.1, L1.1, U3.3
unnamed: C7.2, U1.1, U4.6
unnamed: C9.1, L1.2
unnamed: C10.2, L4.2
unnamed: C11.2, L5.2, L6.1
unnamed: C12.2, C13.1, L6.2, L7.1
unnamed: C13.2, C15.1, C16.2, L7.2, L8.1, R3.1
unnamed: C14.2, L8.2
unnamed: C8.1, C17.1, L2.2, U4.15
unnamed: C17.2, U4.16
unnamed: C18.1, R30.1, U4.1
unnamed: C20.1, L3.2, U4.4
unnamed: C21.1, Q1.1, R4.1, R5.1
unnamed: C22.1, Q2.1, R12.1, R13.1
unnamed: C23.1, Q3.1, R20.1, R21.1
unnamed: C24.2, Y1.1
unnamed: C25.2, Y1.2
unnamed: D1.2, Q1.3, Rel1.1
unnamed: D2.2, Q2.3, Rel2.1
unnamed: D3.2, Rel3.1
unnamed: J1.1, Rel3.3
unnamed: L4.1, L5.1, R1.1, U4.14
unnamed: R6.1, R7.1, R8.2, R9.2, Rel1.4
unnamed: R8.1, R9.1, R10.1, R11.1, Rel1.5
unnamed: R14.1, R15.1, R16.2, R17.2, Rel2.4
unnamed: R16.1, R17.1, R18.1, R19.1, Rel2.5
unnamed: R22.1, R23.1, R24.2, R25.2, Rel3.4
unnamed: R24.1, R25.1, R26.1, R27.1, Rel3.5
unnamed: Rel1.2, Rel1.7
unnamed: Rel1.3, Rel2.6
unnamed: Rel2.2, Rel2.7
unnamed: Rel2.3, Rel3.6
unnamed: Rel3.2, Rel3.7
PSEL0: R28.2, U4.12
PSEL1: R2.2, U4.11
RF_DDS: C15.2, C16.1, Rel1.6
VCC: C1.2, C2.1, C3.1, U1.5, U1.8, U2.1, U3.1
